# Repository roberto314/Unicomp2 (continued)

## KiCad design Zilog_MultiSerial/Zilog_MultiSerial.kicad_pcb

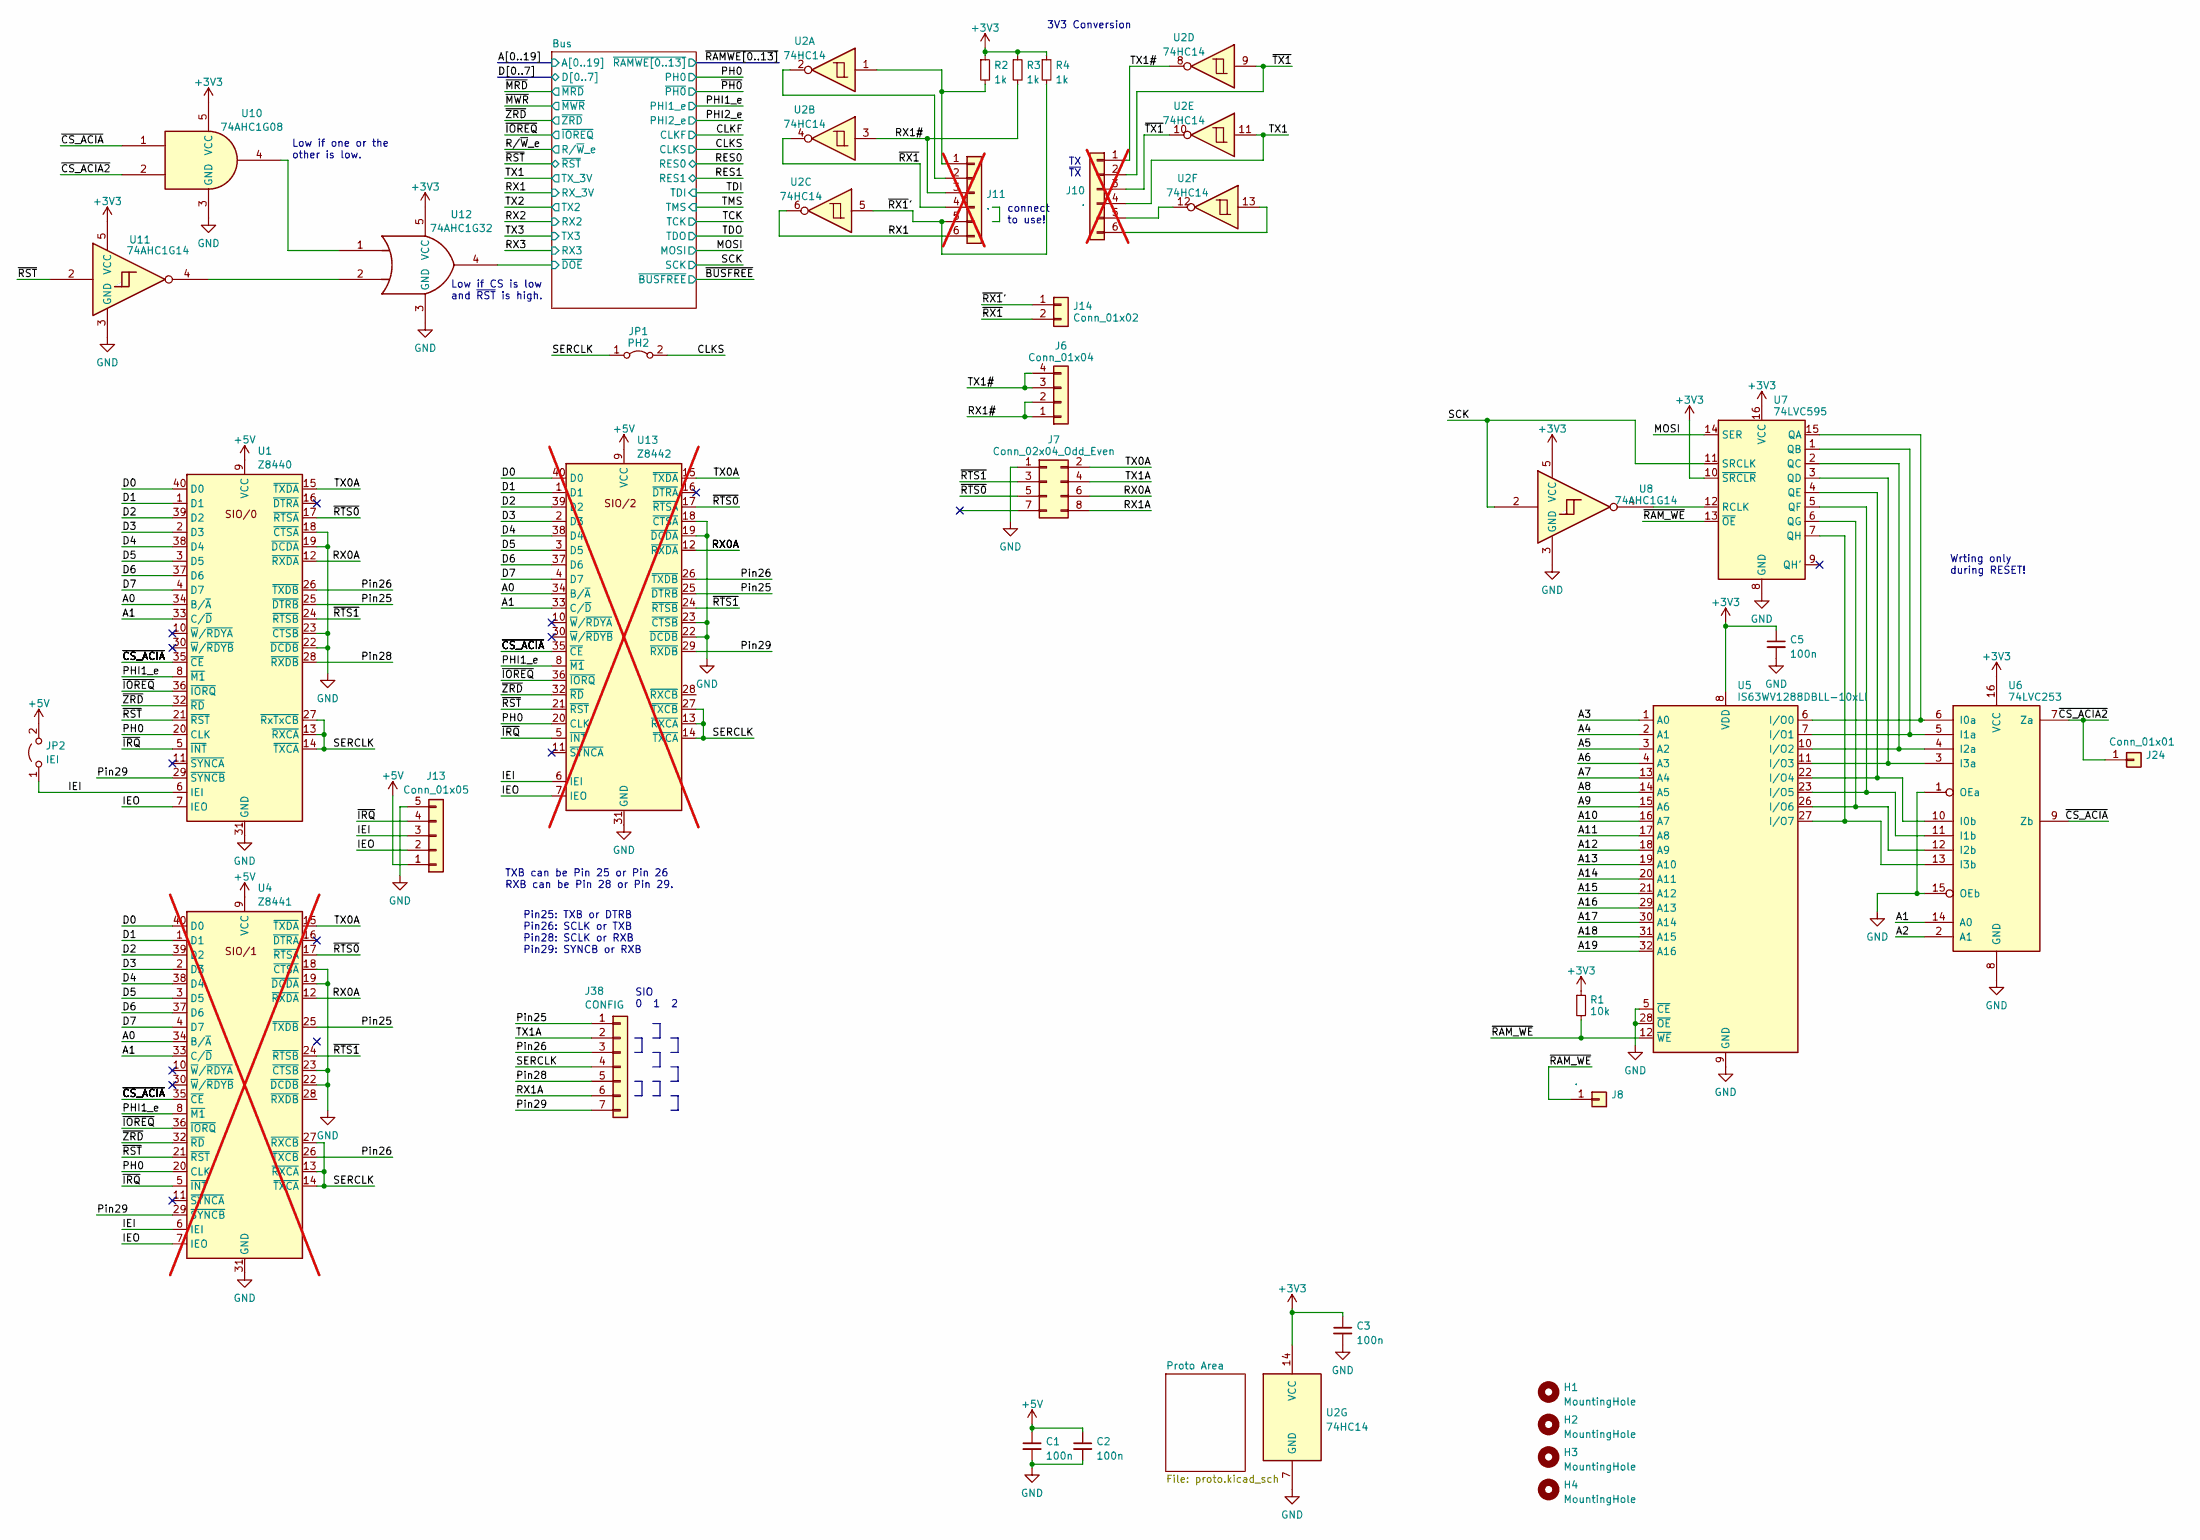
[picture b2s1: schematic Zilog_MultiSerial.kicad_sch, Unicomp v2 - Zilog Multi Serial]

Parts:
C1, C2, C3, C5: 100n; C_1206_3216Metric
H1, H2, H3, H4: MountingHole; MountingHole_3.2mm_M3
J6: Conn_01x04; PinHeader_1x04_P2.54mm_Vertical
J7: Conn_02x04_Odd_Even; PinHeader_2x04_P2.54mm_Vertical
J8: .; PinHeader_1x01_P2.00mm_Vertical
J10, J11: .; PinHeader_1x06_P2.54mm_Vertical; not fitted
J13: Conn_01x05; PinHeader_1x05_P2.54mm_Vertical
J14: Conn_01x02; PinHeader_1x02_P2.54mm_Vertical
J24: Conn_01x01; PinHeader_1x01_P2.00mm_Vertical
J38: CONFIG; PinHeader_1x07_P2.54mm_Vertical
JP1: PH2; SolderJumper-2_P1.3mm_Bridged_RoundedPad1.0x1.5mm
JP2: IEI; PinHeader_1x02_P2.54mm_Vertical
R1: 10k; R_1206_3216Metric_Pad1.30x1.75mm_HandSolder
R2, R3, R4: 1k; R_1206_3216Metric_Pad1.30x1.75mm_HandSolder
U1: Z8440; DIP-40_W15.24mm
U2: 74HC14; DIP-14_W7.62mm_Socket
U4: Z8441; DIP-40_W15.24mm; not fitted
U5: IS63WV1288DBLL-10xLI; TSOP-II-32_21.0x10.2mm_P1.27mm
U6: 74LVC253; SO-16_3.9x9.9mm_P1.27mm
U7: 74LVC595; SO-16_3.9x9.9mm_P1.27mm
U8: 74AHC1G14; SOT-23-5
U10: 74AHC1G08; SOT-23-5_HandSoldering
U11: 74AHC1G14; SOT-23-5_HandSoldering
U12: 74AHC1G32; SOT-23-5_HandSoldering
U13: Z8442; DIP-40_W15.24mm; not fitted

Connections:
+3V3: C3.1, C5.1, R1.1, R2.1, R3.1, R4.1, U2.14 (VCC), U5.8 (VDD), U5.24 (VDD), U6.16 (VCC), U7.10 (~SRCLR), U7.16 (VCC), U8.5 (VCC), U10.5 (VCC), U11.5 (VCC), U12.5 (VCC); also elsewhere on the board
+5V: C1.1, C2.1, J13.1, JP2.2 (B), U1.9 (VCC), U4.9 (VCC), U13.9 (VCC); also elsewhere on the board
/A0: U1.34 (B/~A), U4.34 (B/~A), U13.34 (B/~A); also elsewhere on the board
/A1: U1.33 (C/~D), U4.33 (C/~D), U6.14 (A0), U13.33 (C/~D); also elsewhere on the board
/A2: U6.2 (A1); also elsewhere on the board
/A3: U5.1 (A0); also elsewhere on the board
/A4: U5.2 (A1); also elsewhere on the board
/A5: U5.3 (A2); also elsewhere on the board
/A6: U5.4 (A3); also elsewhere on the board
/A7: U5.13 (A4); also elsewhere on the board
/A8: U5.14 (A5); also elsewhere on the board
/A9: U5.15 (A6); also elsewhere on the board
/A10: U5.16 (A7); also elsewhere on the board
/A11: U5.17 (A8); also elsewhere on the board
/A12: U5.18 (A9); also elsewhere on the board
/A13: U5.19 (A10); also elsewhere on the board
/A14: U5.20 (A11); also elsewhere on the board
/A15: U5.21 (A12); also elsewhere on the board
/A16: U5.29 (A13); also elsewhere on the board
/A17: U5.30 (A14); also elsewhere on the board
/A18: U5.31 (A15); also elsewhere on the board
/A19: U5.32 (A16); also elsewhere on the board
/Bus/~DOE: U12.4; also elsewhere on the board
/CLKS: JP1.2 (B); also elsewhere on the board
/D0: U1.40 (D0), U4.40 (D0), U13.40 (D0); also elsewhere on the board
/D1: U1.1 (D1), U4.1 (D1), U13.1 (D1); also elsewhere on the board
/D2: U1.39 (D2), U4.39 (D2), U13.39 (D2); also elsewhere on the board
/D3: U1.2 (D3), U4.2 (D3), U13.2 (D3); also elsewhere on the board
/D4: U1.38 (D4), U4.38 (D4), U13.38 (D4); also elsewhere on the board
/D5: U1.3 (D5), U4.3 (D5), U13.3 (D5); also elsewhere on the board
/D6: U1.37 (D6), U4.37 (D6), U13.37 (D6); also elsewhere on the board
/D7: U1.4 (D7), U4.4 (D7), U13.4 (D7); also elsewhere on the board
/IEI: J13.3, JP2.1 (A), U1.6 (IEI), U4.6 (IEI), U13.6 (IEI)
/IEO: J13.2, U1.7 (IEO), U4.7 (IEO), U13.7 (IEO)
/MOSI: U7.14 (SER); also elsewhere on the board
/PH0: U1.20 (CLK), U4.20 (CLK), U13.20 (CLK); also elsewhere on the board
/PHI1_e: U1.8 (~M1), U4.8 (~M1), U13.8 (~M1); also elsewhere on the board
/Pin25: J38.1, U1.25 (~DTRB), U4.25 (~TXDB), U13.25 (~DTRB)
/Pin26: J38.3, U1.26 (~TXDB), U4.26 (~TXCB), U13.26 (~TXDB)
/Pin28: J38.5, U1.28 (~RXDB)
/Pin29: J38.7, U1.29 (~SYNCB), U4.29 (~SYNCB), U13.29 (~RXDB)
/RX0A: J7.6, U1.12 (~RXDA), U4.12 (~RXDA), U13.12 (~RXDA)
/RX1: J11.6, U2.6; also elsewhere on the board
/RX1#: J6.1, J6.2, J11.3, R3.2, U2.3
/RX1A: J7.8, J38.6
/SCK: U7.11 (SRCLK), U8.2; also elsewhere on the board
/SERCLK: J38.4, JP1.1 (A), U1.13 (~RXCA), U1.14 (~TXCA), U1.27 (~RxTxCB), U4.13 (~RXCA), U4.14 (~TXCA), U4.27 (~RXCB), U13.13 (~RXCA), U13.14 (~TXCA), U13.27 (~TXCB)
/TX0A: J7.2, U1.15 (~TXDA), U4.15 (~TXDA), U13.15 (~TXDA)
/TX1: J10.4, U2.11; also elsewhere on the board
/TX1#: J6.3, J6.4, J10.1, U2.8
/TX1A: J7.4, J38.2
/~CS_ACIA2: J24.1, U6.7 (Za), U10.2
/~CS_ACIA: U1.35 (~CE), U4.35 (~CE), U6.9 (Zb), U10.1, U13.35 (~CE)
/~IOREQ: U1.36 (~IORQ), U4.36 (~IORQ), U13.36 (~IORQ); also elsewhere on the board
/~IRQ: J13.4, U1.5 (~INT), U4.5 (~INT), U13.5 (~INT)
/~RAM_WE: J8.1, R1.2, U5.12 (~WE), U7.13 (~OE)
/~RST: U1.21 (~RST), U4.21 (~RST), U11.2, U13.21 (~RST); also elsewhere on the board
/~RTS0: J7.5, U1.17 (~RTSA), U4.17 (~RTSA), U13.17 (~RTSA)
/~RTS1: J7.3, U1.24 (~RTSB), U4.24 (~RTSB), U13.24 (~RTSB)
/~RX1: J11.4, J14.2, U2.4
/~RX1': J11.5, J14.1, R4.2, U2.5
/~TX1: J10.2, J10.3, U2.9, U2.10
/~ZRD: U1.32 (~RD), U4.32 (~RD), U13.32 (~RD); also elsewhere on the board
GND: C1.2, C2.2, C3.2, C5.2, J7.1, J13.5, U1.18 (~CTSA), U1.19 (~DCDA), U1.22 (~DCDB), U1.23 (~CTSB), U1.31 (GND), U2.7 (GND), U4.18 (~CTSA), U4.19 (~DCDA), U4.22 (~DCDB), U4.23 (~CTSB), U4.31 (GND), U5.5 (~CE), U5.9 (GND), U5.25 (GND), U5.28 (~OE), U6.1 (OEa), U6.8 (GND), U6.15 (OEb), U7.8 (GND), U8.3 (GND), U10.3 (GND), U11.3 (GND), U12.3 (GND), U13.18 (~CTSA), U13.19 (~DCDA), U13.22 (~DCDB), U13.23 (~CTSB), U13.31 (GND); also elsewhere on the board
unnamed: J11.1, R2.2, U2.1
unnamed: J11.2, U2.2
unnamed: J10.5, U2.12
unnamed: J10.6, U2.13
unnamed: U5.6 (I/O0), U6.6 (I0a), U7.15 (QA)
unnamed: U5.7 (I/O1), U6.5 (I1a), U7.1 (QB)
unnamed: U5.10 (I/O2), U6.4 (I2a), U7.2 (QC)
unnamed: U5.11 (I/O3), U6.3 (I3a), U7.3 (QD)
unnamed: U5.22 (I/O4), U6.10 (I0b), U7.4 (QE)
unnamed: U5.23 (I/O5), U6.11 (I1b), U7.5 (QF)
unnamed: U5.26 (I/O6), U6.12 (I2b), U7.6 (QG)
unnamed: U5.27 (I/O7), U6.13 (I3b), U7.7 (QH)
unnamed: U7.12 (RCLK), U8.4
unnamed: U10.4, U12.1
unnamed: U11.4, U12.2

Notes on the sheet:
TXB can be Pin 25 or Pin 26 RXB can be Pin 28 or Pin 29.
SIO 0 1 2
Wrting only during RESET!
connect to use!
Pin25: TXB or DTRB Pin26: SCLK or TXB Pin28: SCLK or RXB Pin29: SYNCB or RXB
3V3 Conversion
Low if CS is low and ~{RST} is high.
Low if one or the other is low.
TX ~{TX}

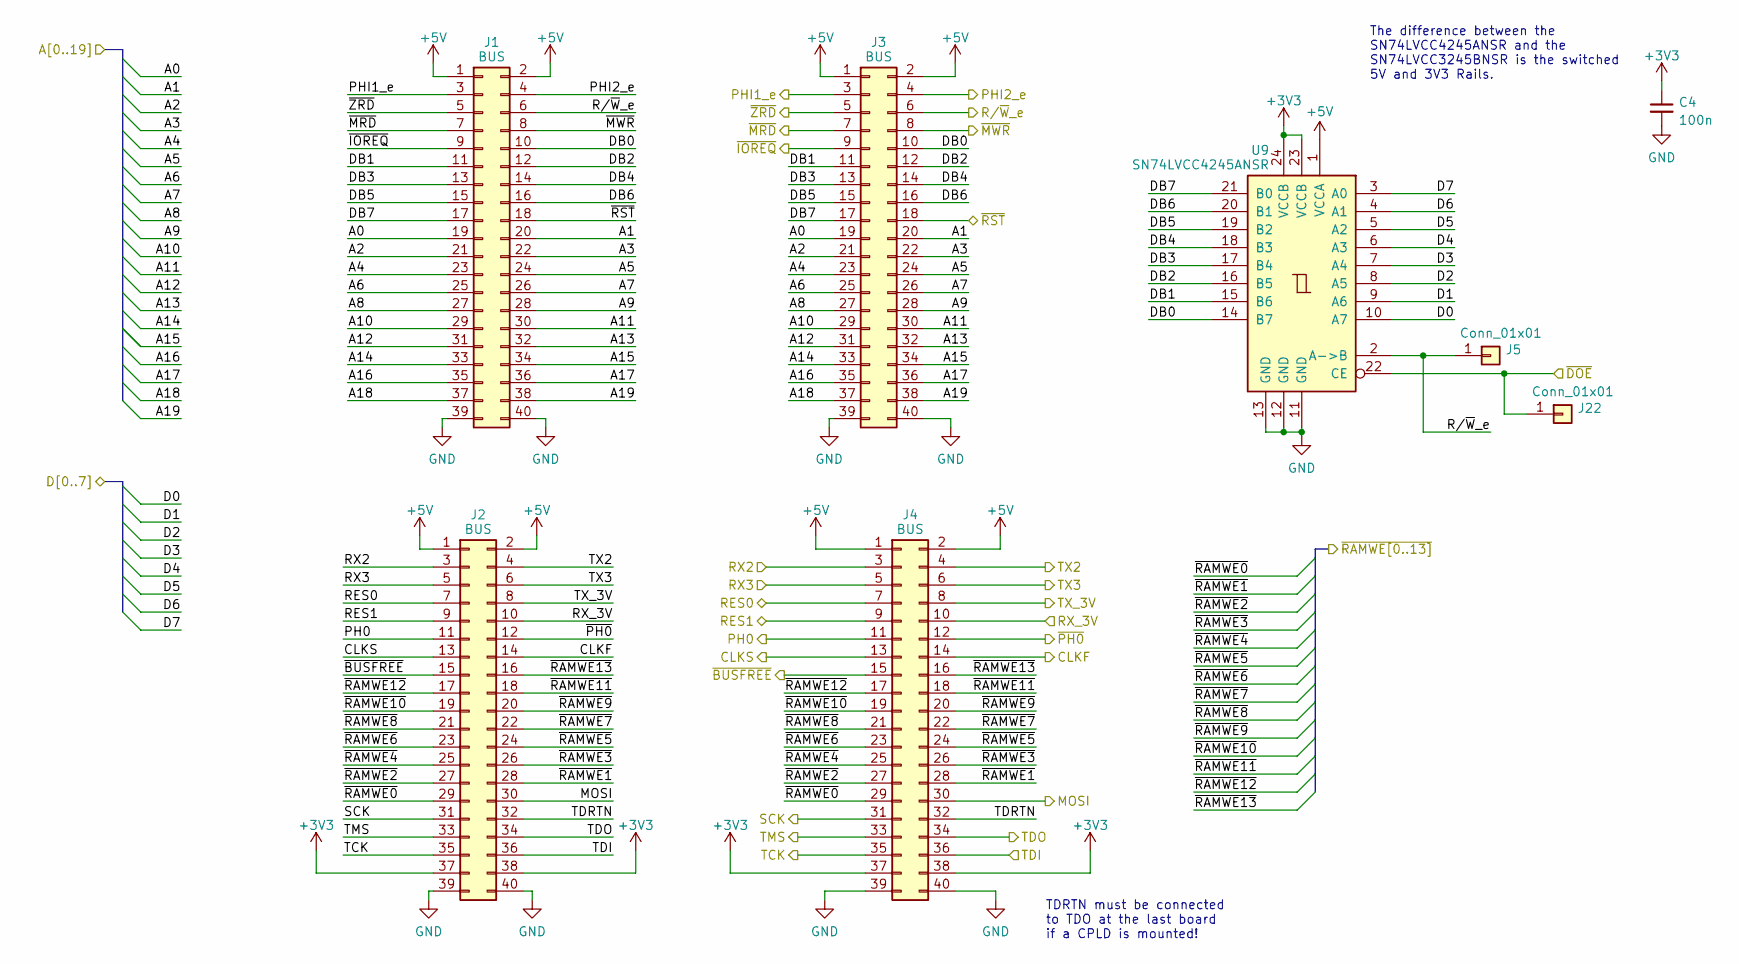
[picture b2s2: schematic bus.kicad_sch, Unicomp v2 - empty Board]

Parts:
C4: 100n; C_1206_3216Metric
J1, J2, J3, J4: BUS; PinSocket_2x20_P2.54mm_Vertical
J5, J22: Conn_01x01; PinHeader_1x01_P2.00mm_Vertical
U9: SN74LVCC4245ANSR; SO-24_5.3x15mm_P1.27mm

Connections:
+3V3: C4.1, J2.37, J2.38, J4.37, J4.38, U9.23 (VCCB), U9.24 (VCCB); also elsewhere on the board
+5V: J1.1, J1.2, J2.1, J2.2, J3.1, J3.2, J4.1, J4.2, U9.1 (VCCA); also elsewhere on the board
/A0: J1.19, J3.19; also elsewhere on the board
/A1: J1.20, J3.20; also elsewhere on the board
/A2: J1.21, J3.21; also elsewhere on the board
/A3: J1.22, J3.22; also elsewhere on the board
/A4: J1.23, J3.23; also elsewhere on the board
/A5: J1.24, J3.24; also elsewhere on the board
/A6: J1.25, J3.25; also elsewhere on the board
/A7: J1.26, J3.26; also elsewhere on the board
/A8: J1.27, J3.27; also elsewhere on the board
/A9: J1.28, J3.28; also elsewhere on the board
/A10: J1.29, J3.29; also elsewhere on the board
/A11: J1.30, J3.30; also elsewhere on the board
/A12: J1.31, J3.31; also elsewhere on the board
/A13: J1.32, J3.32; also elsewhere on the board
/A14: J1.33, J3.33; also elsewhere on the board
/A15: J1.34, J3.34; also elsewhere on the board
/A16: J1.35, J3.35; also elsewhere on the board
/A17: J1.36, J3.36; also elsewhere on the board
/A18: J1.37, J3.37; also elsewhere on the board
/A19: J1.38, J3.38; also elsewhere on the board
/Bus/DB0: J1.10, J3.10, U9.14 (B7)
/Bus/DB1: J1.11, J3.11, U9.15 (B6)
/Bus/DB2: J1.12, J3.12, U9.16 (B5)
/Bus/DB3: J1.13, J3.13, U9.17 (B4)
/Bus/DB4: J1.14, J3.14, U9.18 (B3)
/Bus/DB5: J1.15, J3.15, U9.19 (B2)
/Bus/DB6: J1.16, J3.16, U9.20 (B1)
/Bus/DB7: J1.17, J3.17, U9.21 (B0)
/Bus/TDRTN: J2.32, J4.32
/Bus/~DOE: J22.1, U9.22 (CE); also elsewhere on the board
/CLKF: J2.14, J4.14
/CLKS: J2.13, J4.13; also elsewhere on the board
/D0: U9.10 (A7); also elsewhere on the board
/D1: U9.9 (A6); also elsewhere on the board
/D2: U9.8 (A5); also elsewhere on the board
/D3: U9.7 (A4); also elsewhere on the board
/D4: U9.6 (A3); also elsewhere on the board
/D5: U9.5 (A2); also elsewhere on the board
/D6: U9.4 (A1); also elsewhere on the board
/D7: U9.3 (A0); also elsewhere on the board
/MOSI: J2.30, J4.30; also elsewhere on the board
/PH0: J2.11, J4.11; also elsewhere on the board
/PHI1_e: J1.3, J3.3; also elsewhere on the board
/PHI2_e: J1.4, J3.4
/RES0: J2.7, J4.7
/RES1: J2.9, J4.9
/RX1: J2.10, J4.10; also elsewhere on the board
/RX2: J2.3, J4.3
/RX3: J2.5, J4.5
/R/~W_e: J1.6, J3.6, J5.1, U9.2 (A->B)
/SCK: J2.31, J4.31; also elsewhere on the board
/TCK: J2.35, J4.35
/TDI: J2.36, J4.36
/TDO: J2.34, J4.34
/TMS: J2.33, J4.33
/TX1: J2.8, J4.8; also elsewhere on the board
/TX2: J2.4, J4.4
/TX3: J2.6, J4.6
/~BUSFREE: J2.15, J4.15
/~IOREQ: J1.9, J3.9; also elsewhere on the board
/~MRD: J1.7, J3.7
/~MWR: J1.8, J3.8
/~PH0: J2.12, J4.12
/~RAMWE0: J2.29, J4.29
/~RAMWE1: J2.28, J4.28
/~RAMWE2: J2.27, J4.27
/~RAMWE3: J2.26, J4.26
/~RAMWE4: J2.25, J4.25
/~RAMWE5: J2.24, J4.24
/~RAMWE6: J2.23, J4.23
/~RAMWE7: J2.22, J4.22
/~RAMWE8: J2.21, J4.21
/~RAMWE9: J2.20, J4.20
/~RAMWE10: J2.19, J4.19
/~RAMWE11: J2.18, J4.18
/~RAMWE12: J2.17, J4.17
/~RAMWE13: J2.16, J4.16
/~RST: J1.18, J3.18; also elsewhere on the board
/~ZRD: J1.5, J3.5; also elsewhere on the board
GND: C4.2, J1.39, J1.40, J2.39, J2.40, J3.39, J3.40, J4.39, J4.40, U9.11 (GND), U9.12 (GND), U9.13 (GND); also elsewhere on the board

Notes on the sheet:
TDRTN must be connected to TDO at the last board if a CPLD is mounted!
The difference between the SN74LVCC4245ANSR and the SN74LVCC3245BNSR is the switched 5V and 3V3 Rails.

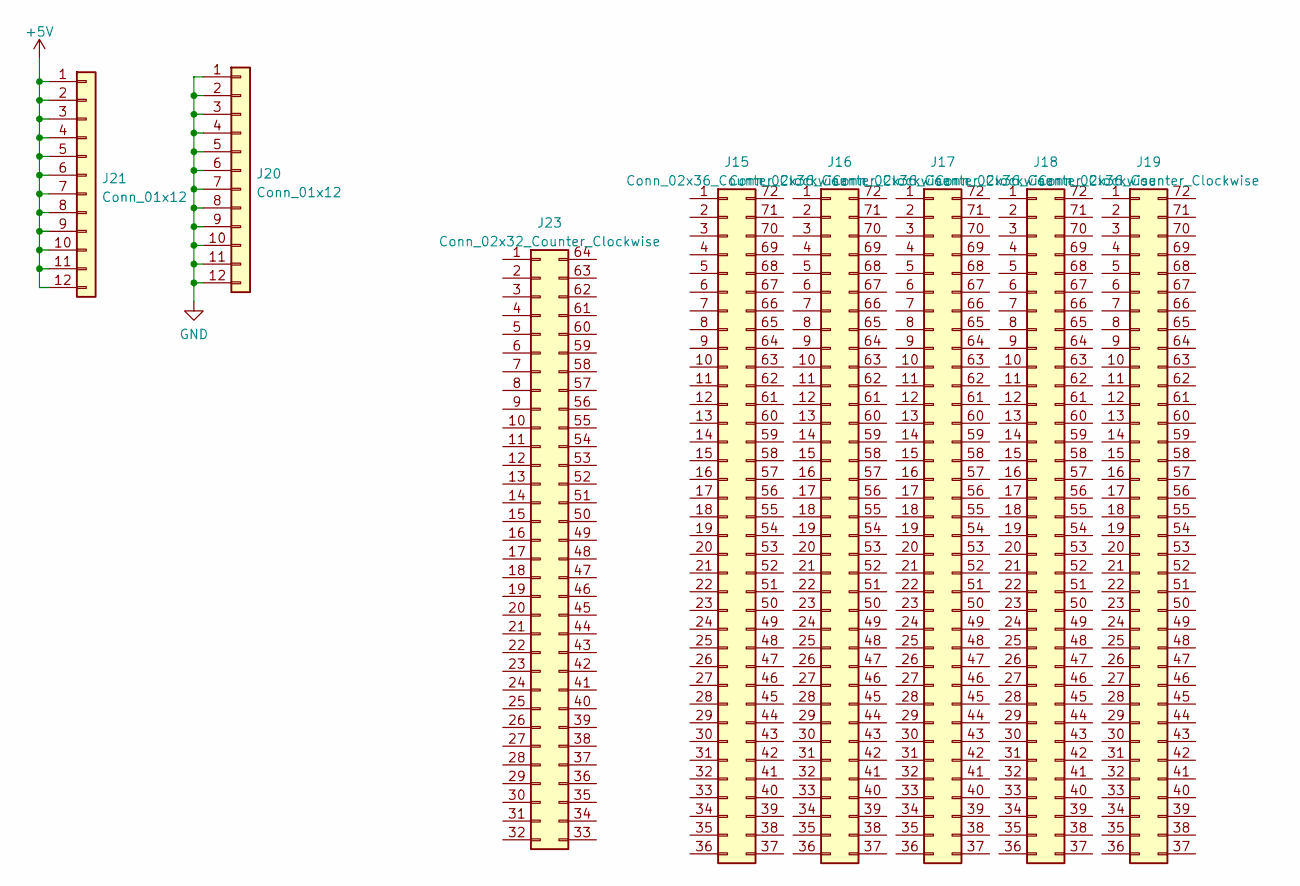
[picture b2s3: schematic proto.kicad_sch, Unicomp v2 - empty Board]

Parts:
J15, J16, J17, J18, J19: Conn_02x36_Counter_Clockwise; Proto_2x36
J20, J21: Conn_01x12; PinHeader_1x12_P2.54mm_Vertical
J23: Conn_02x32_Counter_Clockwise; Proto_2x32

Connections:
+5V: J21.1, J21.2, J21.3, J21.4, J21.5, J21.6, J21.7, J21.8, J21.9, J21.10, J21.11, J21.12; also elsewhere on the board
GND: J20.1, J20.2, J20.3, J20.4, J20.5, J20.6, J20.7, J20.8, J20.9, J20.10, J20.11, J20.12; also elsewhere on the board

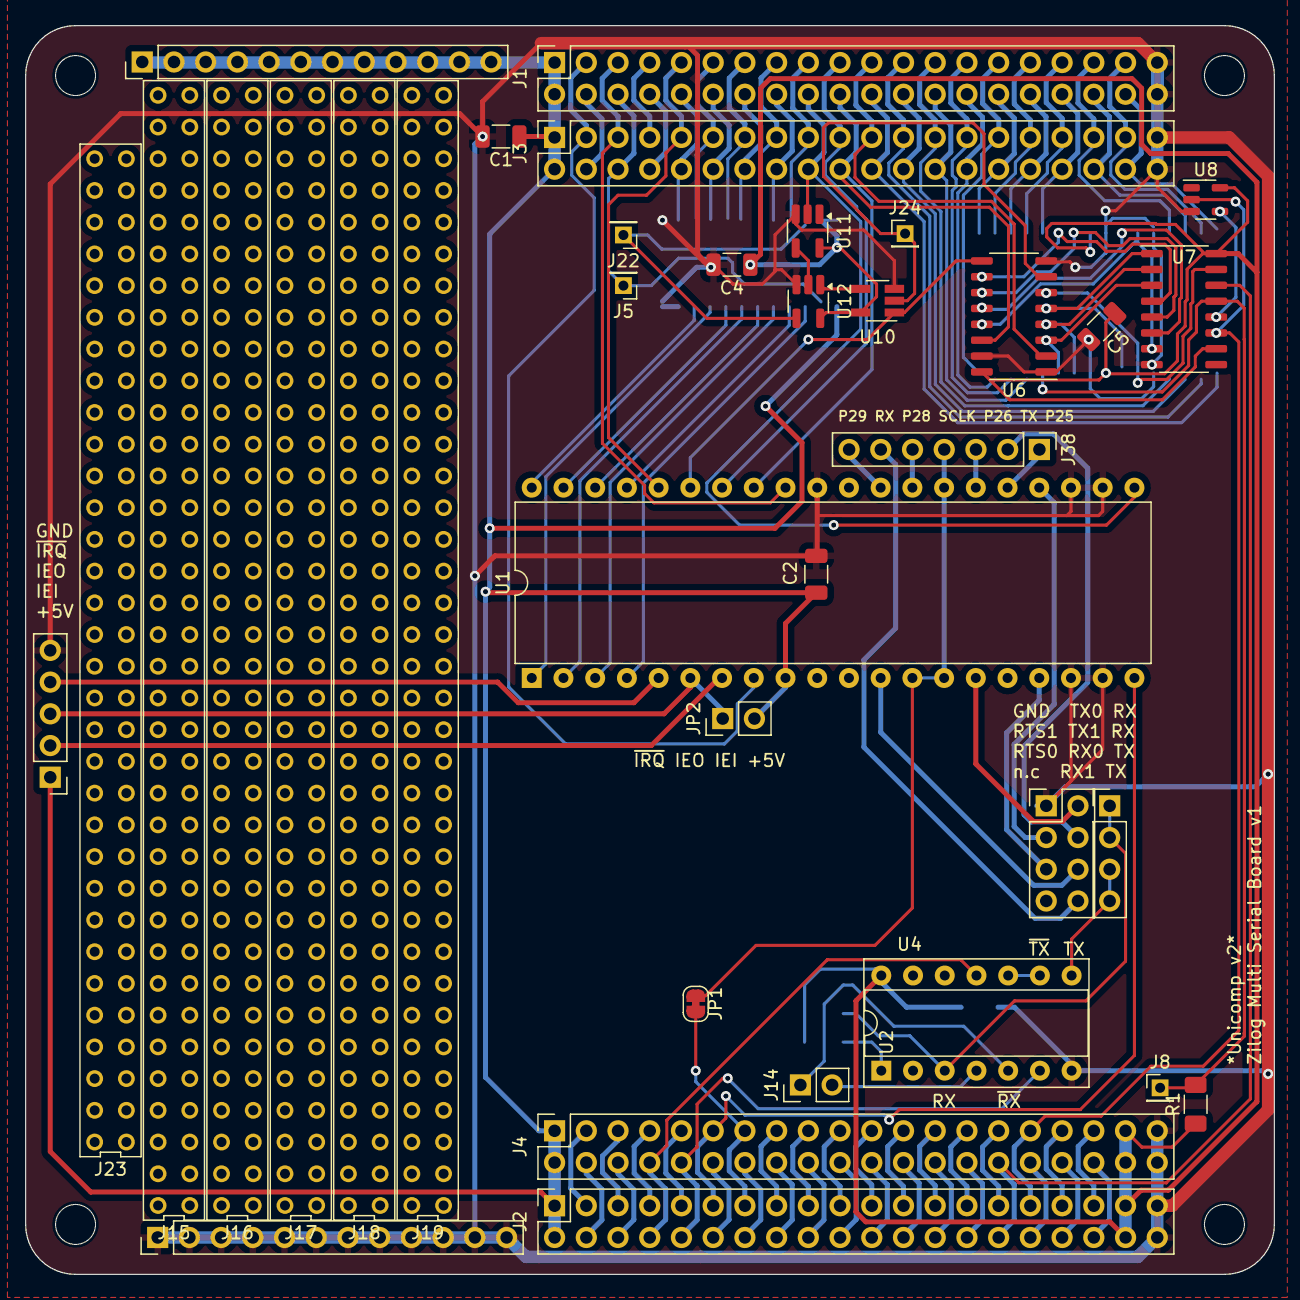
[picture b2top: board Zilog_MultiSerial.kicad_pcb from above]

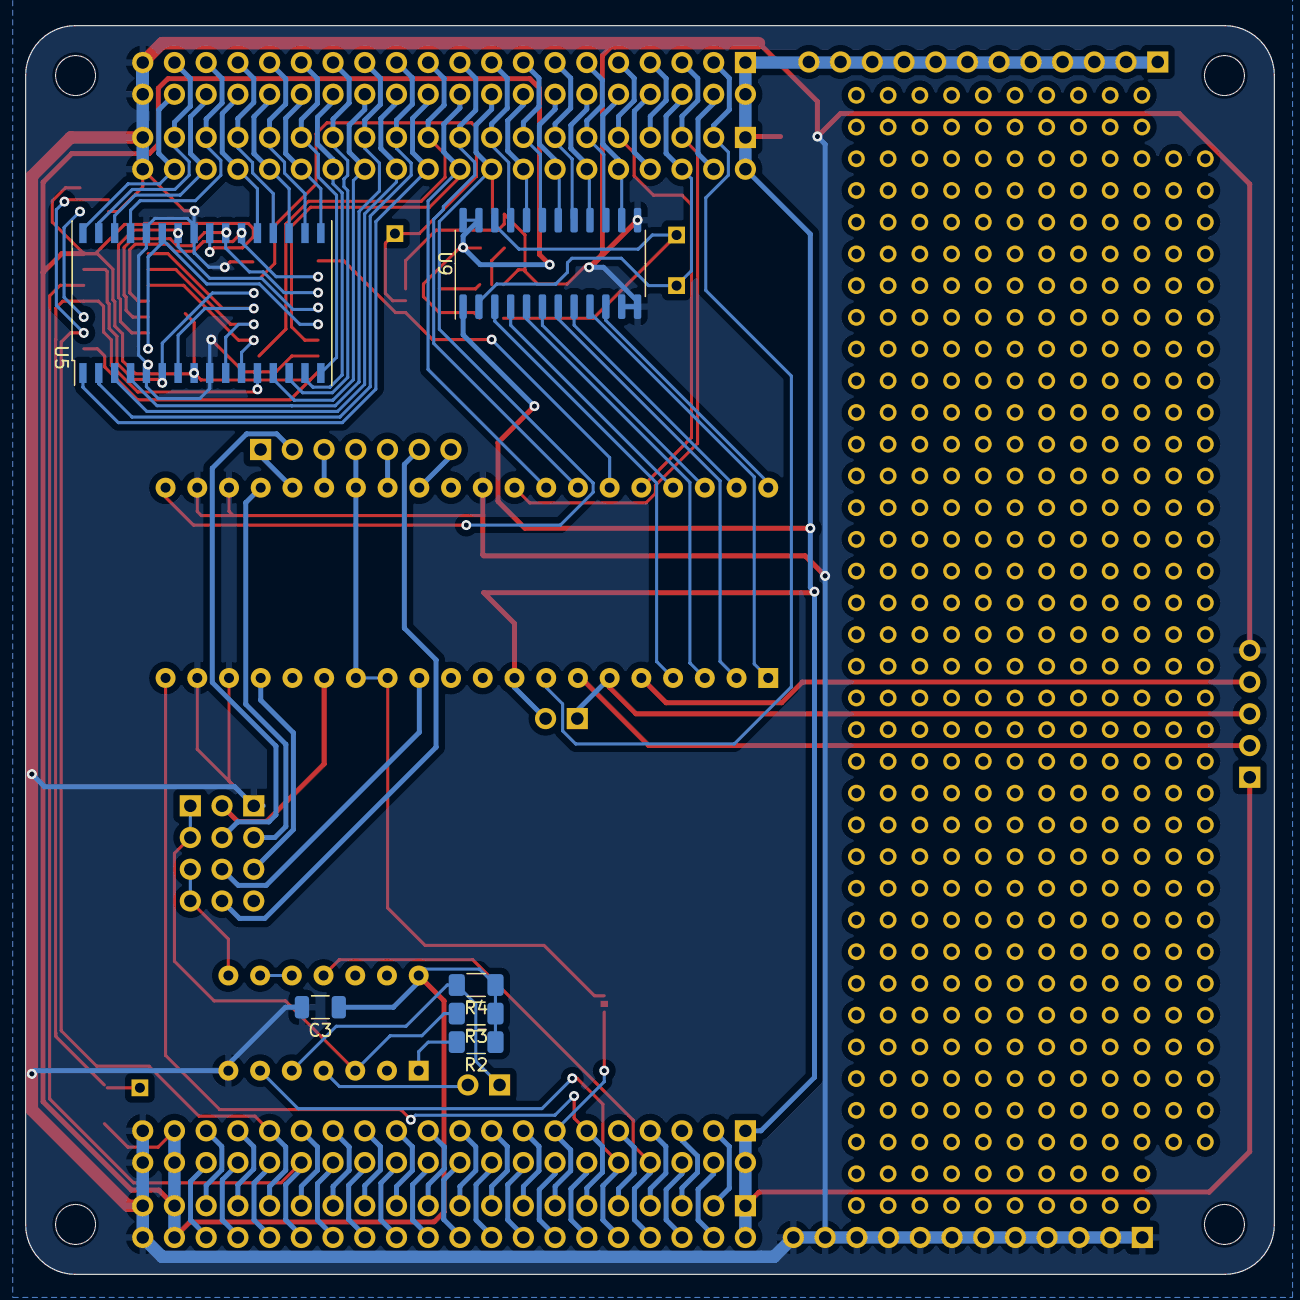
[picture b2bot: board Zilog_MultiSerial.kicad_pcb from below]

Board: 2 copper layers, 100.0 x 100.0 mm, 46 parts (6 on the bottom side), 116 nets.

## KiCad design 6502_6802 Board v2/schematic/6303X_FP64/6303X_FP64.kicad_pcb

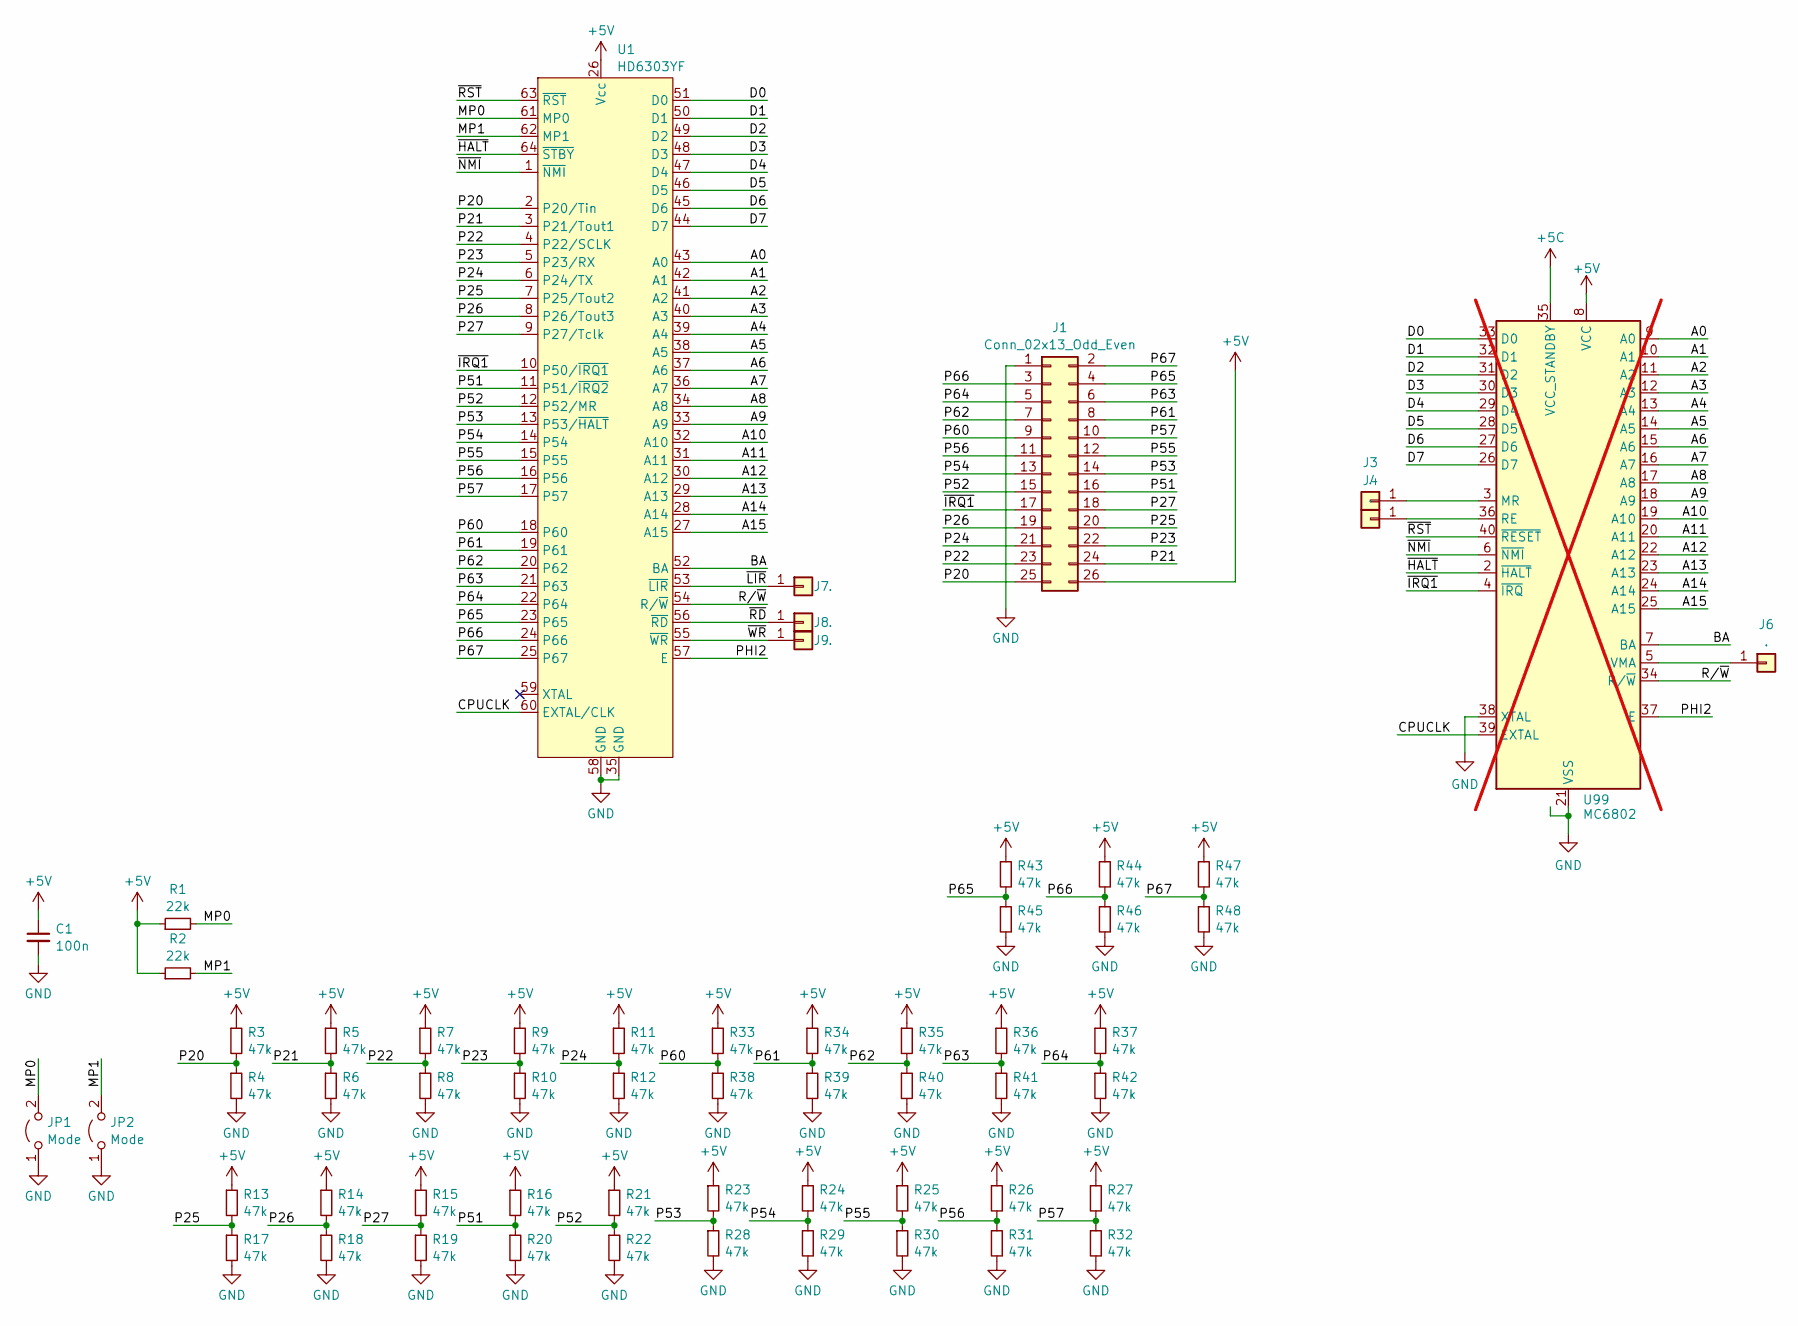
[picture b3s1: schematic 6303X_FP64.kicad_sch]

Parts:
C1: 100n; C_1206_3216Metric_Pad1.33x1.80mm_HandSolder
J1: Conn_02x13_Odd_Even; PinHeader_2x13_P2.54mm_Horizontal
J3, J4, J6, J7, J8, J9: .; PinHeader_1x01_P2.00mm_Vertical
JP1, JP2: Mode; PinHeader_1x02_P2.54mm_Vertical
R1, R2: 22k; R_1206_3216Metric_Pad1.30x1.75mm_HandSolder
R3, R4, R5, R6, R7, R8, R9, R10, R11, R12, R13, R14, R15, R16, R17, R18, R19, R20, R21, R22, R23, R24, R25, R26, R27, R28, R29, R30, R31, R32, R33, R34, R35, R36, R37, R38, R39, R40, R41, R42, R43, R44, R45, R46, R47, R48: 47k; R_1206_3216Metric_Pad1.30x1.75mm_HandSolder
U1: HD6303YF; QFP-64_14x20_Pitch1mm
U99: MC6802; DIP-40_W15.24mm; not fitted

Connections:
+5V: C1.1, J1.26, R1.1, R2.1, R3.1, R5.1, R7.1, R9.1, R11.1, R13.1, R14.1, R15.1, R16.1, R21.1, R23.1, R24.1, R25.1, R26.1, R27.1, R33.1, R34.1, R35.1, R36.1, R37.1, R43.1, R44.1, R47.1, U1.26 (Vcc); also elsewhere on the board
/A0: U1.43 (A0); also elsewhere on the board
/A1: U1.42 (A1); also elsewhere on the board
/A2: U1.41 (A2); also elsewhere on the board
/A3: U1.40 (A3); also elsewhere on the board
/A4: U1.39 (A4); also elsewhere on the board
/A5: U1.38 (A5); also elsewhere on the board
/A6: U1.37 (A6); also elsewhere on the board
/A7: U1.36 (A7); also elsewhere on the board
/A8: U1.34 (A8); also elsewhere on the board
/A9: U1.33 (A9); also elsewhere on the board
/A10: U1.32 (A10); also elsewhere on the board
/A11: U1.31 (A11); also elsewhere on the board
/A12: U1.30 (A12); also elsewhere on the board
/A13: U1.29 (A13); also elsewhere on the board
/A14: U1.28 (A14); also elsewhere on the board
/A15: U1.27 (A15); also elsewhere on the board
/BA: U1.52 (BA); also elsewhere on the board
/CPUCLK: U1.60 (EXTAL/CLK); also elsewhere on the board
/D0: U1.51 (D0); also elsewhere on the board
/D1: U1.50 (D1); also elsewhere on the board
/D2: U1.49 (D2); also elsewhere on the board
/D3: U1.48 (D3); also elsewhere on the board
/D4: U1.47 (D4); also elsewhere on the board
/D5: U1.46 (D5); also elsewhere on the board
/D6: U1.45 (D6); also elsewhere on the board
/D7: U1.44 (D7); also elsewhere on the board
/MP0: JP1.2 (B), R1.2, U1.61 (MP0)
/MP1: JP2.2 (B), R2.2, U1.62 (MP1)
/P20: J1.25, R3.2, R4.1, U1.2 (P20/Tin)
/P21: J1.24, R5.2, R6.1, U1.3 (P21/Tout1)
/P22: J1.23, R7.2, R8.1, U1.4 (P22/SCLK)
/P23: J1.22, R9.2, R10.1, U1.5 (P23/RX)
/P24: J1.21, R11.2, R12.1, U1.6 (P24/TX)
/P25: J1.20, R13.2, R17.1, U1.7 (P25/Tout2)
/P26: J1.19, R14.2, R18.1, U1.8 (P26/Tout3)
/P27: J1.18, R15.2, R19.1, U1.9 (P27/Tclk)
/P51: J1.16, R16.2, R20.1, U1.11 (P51/~IRQ2)
/P52: J1.15, R21.2, R22.1, U1.12 (P52/MR)
/P53: J1.14, R23.2, R28.1, U1.13 (P53/~HALT)
/P54: J1.13, R24.2, R29.1, U1.14 (P54)
/P55: J1.12, R25.2, R30.1, U1.15 (P55)
/P56: J1.11, R26.2, R31.1, U1.16 (P56)
/P57: J1.10, R27.2, R32.1, U1.17 (P57)
/P60: J1.9, R33.2, R38.1, U1.18 (P60)
/P61: J1.8, R34.2, R39.1, U1.19 (P61)
/P62: J1.7, R35.2, R40.1, U1.20 (P62)
/P63: J1.6, R36.2, R41.1, U1.21 (P63)
/P64: J1.5, R37.2, R42.1, U1.22 (P64)
/P65: J1.4, R43.2, R45.1, U1.23 (P65)
/P66: J1.3, R44.2, R46.1, U1.24 (P66)
/P67: J1.2, R47.2, R48.1, U1.25 (P67)
/PHI2: U1.57 (E); also elsewhere on the board
/R/~W: U1.54 (R/~W); also elsewhere on the board
/~HALT: U1.64 (~STBY); also elsewhere on the board
/~IRQ1: J1.17, U1.10 (P50/~IRQ1); also elsewhere on the board
/~LIR: J7.1, U1.53 (~LIR)
/~NMI: U1.1 (~NMI); also elsewhere on the board
/~RD: J8.1, U1.56 (~RD)
/~RST: U1.63 (~RST); also elsewhere on the board
/~WR: J9.1, U1.55 (~WR)
GND: C1.2, J1.1, JP1.1 (A), JP2.1 (A), R4.2, R6.2, R8.2, R10.2, R12.2, R17.2, R18.2, R19.2, R20.2, R22.2, R28.2, R29.2, R30.2, R31.2, R32.2, R38.2, R39.2, R40.2, R41.2, R42.2, R45.2, R46.2, R48.2, U1.35 (GND), U1.58 (GND); also elsewhere on the board
unnamed 63: J3.1; also elsewhere on the board
unnamed 64: J4.1; also elsewhere on the board
unnamed 65: J6.1; also elsewhere on the board
